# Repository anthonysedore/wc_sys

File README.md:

# wc_sys
Wireless Communication System for Electrathon

PCB designed in KiCad,

Code for ESP32 in Arduino

-read data from motor controller, battery BMS
-collect GPS data
-log all data to sdcard
-send data to pitcrew
-show important metrics and any warnings to driver
-enable recording cool videos with data synced to video time

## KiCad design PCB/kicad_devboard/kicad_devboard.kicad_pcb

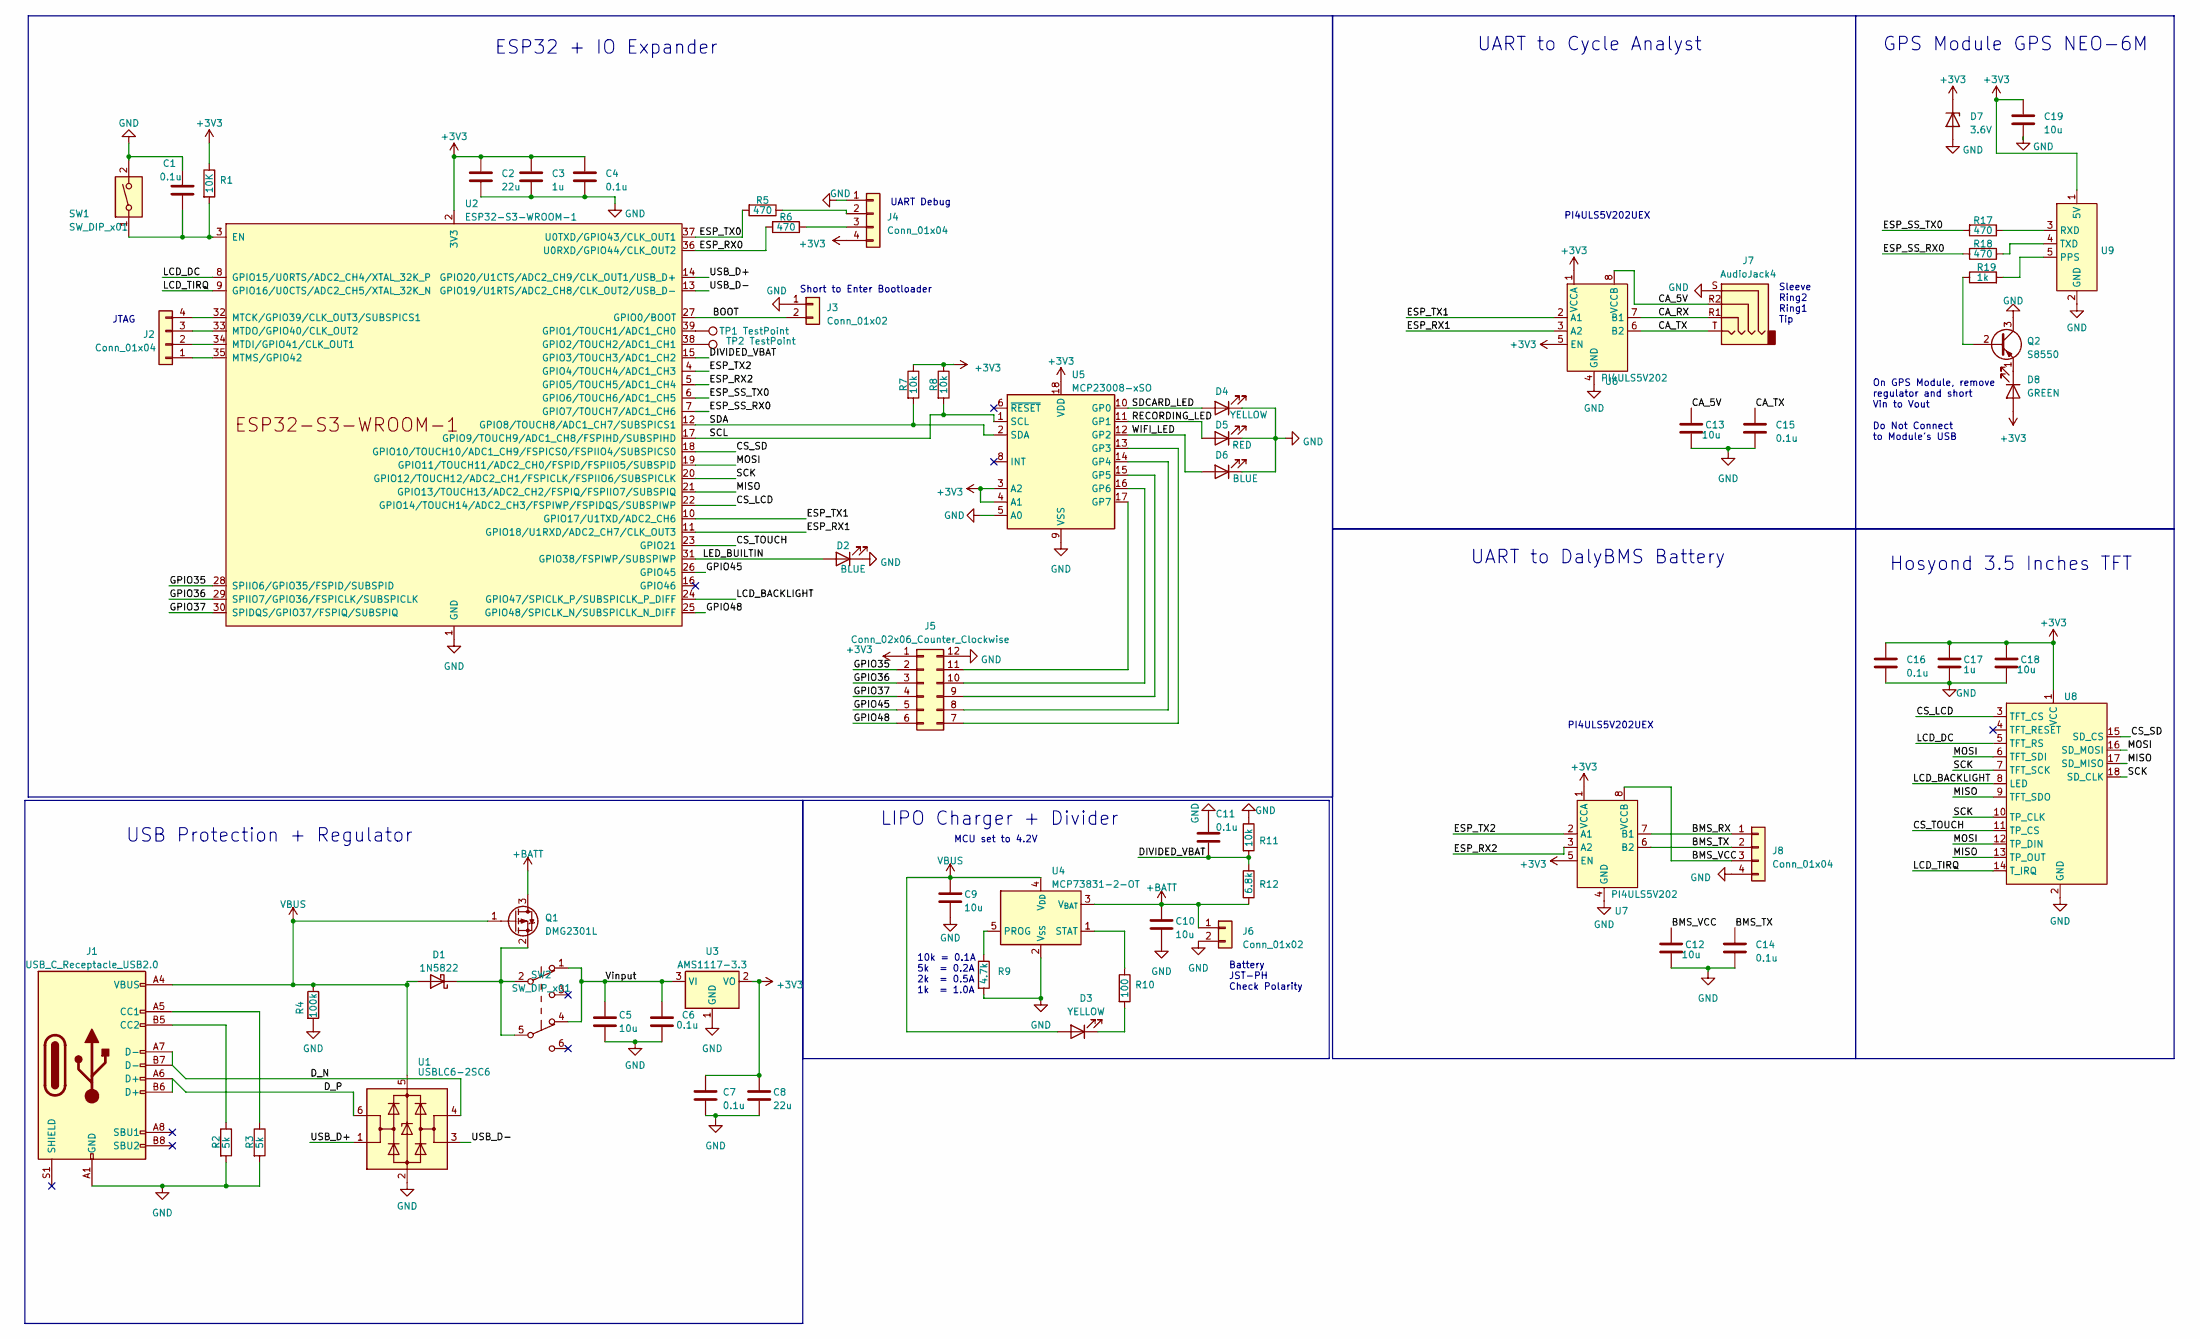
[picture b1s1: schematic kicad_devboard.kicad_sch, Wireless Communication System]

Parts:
C1, C4, C6, C7, C14, C15: 0.1u; C_0603_1608Metric
C2, C8: 22u; C_0603_1608Metric
C3: 1u; C_0603_1608Metric
C5, C19: 10u; C_0603_1608Metric
C9, C10, C12, C13: 10u; C_1206_3216Metric
C11: 0.1u; C_1206_3216Metric
C16: 0.1u; C_0805_2012Metric
C17: 1u; C_0805_2012Metric
C18: 10u; C_0805_2012Metric
D1: 1N5822; D_SMA
D2, D6: BLUE; LED_1206_3216Metric
D3, D4: YELLOW; LED_1206_3216Metric
D5: RED; LED_1206_3216Metric
D7: 3.6V; D_MiniMELF
D8: GREEN; LED_1206_3216Metric
J1: USB_C_Receptacle_USB2.0; USB_C_Receptacle_Palconn_UTC16-G
J2, J4: Conn_01x04; PinSocket_1x04_P2.54mm_Vertical
J3: Conn_01x02; PinHeader_1x02_P2.54mm_Vertical
J5: Conn_02x06_Counter_Clockwise; PinSocket_2x06_P2.54mm_Vertical
J6: Conn_01x02; JST_PH_S2B-PH-K_1x02_P2.00mm_Horizontal
J7: AudioJack4; SJ-43514-SMT_CUD
J8: Conn_01x04; JST_PH_S4B-PH-K_1x04_P2.00mm_Horizontal
Q1: DMG2301L; SOT-23
Q2: S8550; SOT-23
R1: 10K; R_1206_3216Metric
R2, R3: 5k; R_0603_1608Metric
R4: 100k; R_1206_3216Metric
R5, R6, R17, R18: 470; R_1206_3216Metric
R7, R8, R11: 10k; R_1206_3216Metric
R9: 4.7k; R_1206_3216Metric
R10: 100; R_1206_3216Metric
R12: 6.8k; R_1206_3216Metric
R19: 1k; R_1206_3216Metric
SW1: SW_DIP_x01; SW_PUSH_6mm_H5mm
SW2: SW_DIP_x01; SW_E-Switch_EG2219_DPDT_Angled
TP1, TP2: TestPoint; TestPoint_Pad_D4.0mm
U1: USBLC6-2SC6; SOT-23-6
U2: ESP32-S3-WROOM-1; ESP32-S3-WROOM-1U
U3: AMS1117-3.3; SOT-223-3_TabPin2
U4: MCP73831-2-OT; SOT-23-5
U5: MCP23008-xSO; SOIC-18W_7.5x11.6mm_P1.27mm
U6, U7: PI4ULS5V202; PI4ULS5V202UEX
U8: 3.5_inch_SPI_Module_ILI9488
U9: GT-U7

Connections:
+3V3: C2.1, C3.1, C4.1, C7.1, C8.1, C16.1, C17.1, C18.1, C19.1, D7.1 (K), D8.2 (A), J4.4, J5.1, R1.1, R7.1, R8.1, U2.2 (3V3), U3.2 (VO), U5.3 (A2), U5.4 (A1), U5.18 (VDD), U6.1 (VCCA), U6.5 (EN), U7.1 (VCCA), U7.5 (EN), U8.1 (VCC), U9.1 (5V)
+BATT: C10.1, J6.1, Q1.3 (D), R12.2, U4.3 (V_{BAT})
/BMS_RX: J8.1, U7.7 (B1)
/BMS_TX: C14.1, J8.2, U7.6 (B2)
/BMS_VCC: C12.1, J8.3, U7.8 (VCCB)
/BOOT: J3.2, U2.27 (GPIO0/BOOT)
/CA_5V: C13.1, J7.R2, U6.8 (VCCB)
/CA_RX: J7.R1, U6.7 (B1)
/CA_TX: C15.1, J7.T, U6.6 (B2)
/CS_LCD: U2.22 (GPIO14/TOUCH14/ADC2_CH3/FSPIWP/FSPIDQS/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), U8.3 (TFT_CS)
/CS_SD: U2.18 (GPIO10/TOUCH10/ADC1_CH9/FSPICS0/FSPIIO4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), U8.15 (SD_CS)
/CS_TOUCH: U2.23 (GPIO21), U8.11 (TP_CS)
/DIVIDED_VBAT: C11.2, R11.2, R12.1, U2.15 (GPIO3/TOUCH3/ADC1_CH2)
/ESP_RX0: R6.2, U2.36 (U0RXD/GPIO44/CLK_OUT2)
/ESP_RX1: U2.11 (GPIO18/U1RXD/ADC2_CH7/CLK_OUT3), U6.3 (A2)
/ESP_RX2: U2.5 (GPIO5/TOUCH5/ADC1_CH4), U7.3 (A2)
/ESP_SS_RX0: R18.2, U2.7 (GPIO7/TOUCH7/ADC1_CH6)
/ESP_SS_TX0: R17.2, U2.6 (GPIO6/TOUCH6/ADC1_CH5)
/ESP_TX0: R5.2, U2.37 (U0TXD/GPIO43/CLK_OUT1)
/ESP_TX1: U2.10 (GPIO17/U1TXD/ADC2_CH6), U6.2 (A1)
/ESP_TX2: U2.4 (GPIO4/TOUCH4/ADC1_CH3), U7.2 (A1)
/GPIO35: J5.2, U2.28 (SPIIO6/GPIO35/FSPID/SUBSPID)
/GPIO36: J5.3, U2.29 (SPIIO7/GPIO36/FSPICLK/SUBSPICLK)
/GPIO37: J5.4, U2.30 (SPIDQS/GPIO37/FSPIQ/SUBSPIQ)
/GPIO45: J5.5, U2.26 (GPIO45)
/GPIO48: J5.6, U2.25 (GPIO48/SPICLK_N/SUBSPICLK_N_DIFF)
/LCD_BACKLIGHT: U2.24 (GPIO47/SPICLK_P/SUBSPICLK_P_DIFF), U8.8 (LED)
/LCD_DC: U2.8 (GPIO15/U0RTS/ADC2_CH4/XTAL_32K_P), U8.5 (TFT_RS)
/LCD_TIRQ: U2.9 (GPIO16/U0CTS/ADC2_CH5/XTAL_32K_N), U8.14 (T_IRQ)
/LED_BUILTIN: D2.2 (A), U2.31 (GPIO38/FSPIWP/SUBSPIWP)
/MISO: U2.21 (GPIO13/TOUCH13/ADC2_CH2/FSPIQ/FSPIIO7/S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), U8.9 (TFT_SDO), U8.13 (TP_OUT), U8.17 (SD_MISO)
/MOSI: U2.19 (GPIO11/TOUCH11/ADC2_CH0/FSPID/FSPIIO5/S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), U8.6 (TFT_SDI), U8.12 (TP_DIN), U8.16 (SD_MOSI)
/RECORDING_LED: D5.2 (A), U5.11 (GP1)
/SCK: U2.20 (GPIO12/TOUCH12/ADC2_CH1/FSPICLK/FSPIIO6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), U8.7 (TFT_SCK), U8.10 (TP_CLK), U8.18 (SD_CLK)
/SCL: R8.2, U2.17 (GPIO9/TOUCH9/ADC1_CH8/FSPIHD/SUBSPIHD), U5.1 (SCL)
/SDA: R7.2, U2.12 (GPIO8/TOUCH8/ADC1_CH7/SUBSPICS1), U5.2 (SDA)
/SDCARD_LED: D4.2 (A), U5.10 (GP0)
/USB_D+: U1.1 (I/O1), U2.14 (GPIO20/U1CTS/ADC2_CH9/CLK_OUT1/USB_D+)
/USB_D-: U1.3 (I/O2), U2.13 (GPIO19/U1RTS/ADC2_CH8/CLK_OUT2/USB_D-)
/Vinput: C5.1, C6.2, SW2.1 (A), SW2.4 (A), U3.3 (VI)
/WIFI_LED: D6.2 (A), U5.12 (GP2)
GND: C1.1, C2.2, C3.2, C4.2, C5.2, C6.1, C7.2, C8.2, C9.2, C10.2, C11.1, C12.2, C13.2, C14.2, C15.2, C16.2, C17.2, C18.2, C19.2, D2.1 (K), D4.1 (K), D5.1 (K), D6.1 (K), D7.2 (A), J1.A1 (GND), J1.A12 (GND), J1.B1 (GND), J1.B12 (GND), J3.1, J4.1, J5.12, J6.2, J7.S, J8.4, Q2.3 (C), R2.2, R3.2, R4.2, R9.2, R11.1, SW1.2, U1.2 (GND), U2.1 (GND), U2.40 (GND), U2.41 (GND), U3.1 (GND), U4.2 (V_{SS}), U5.5 (A0), U5.9 (VSS), U6.4 (GND), U7.4 (GND), U8.2 (GND), U9.2 (GND)
unnamed: D1.1 (K), Q1.2 (S), SW2.2 (B), SW2.5 (B)
unnamed: D3.1 (K), R10.2
unnamed: D8.1 (K), Q2.1 (E)
unnamed: J1.A5 (CC1), R3.1
unnamed: J1.B5 (CC2), R2.1
unnamed: J2.1, U2.35 (MTMS/GPIO42)
unnamed: J2.2, U2.34 (MTDI/GPIO41/CLK_OUT1)
unnamed: J2.3, U2.33 (MTDO/GPIO40/CLK_OUT2)
unnamed: J2.4, U2.32 (MTCK/GPIO39/CLK_OUT3/SUBSPICS1)
unnamed: J4.2, R5.1
unnamed: J4.3, R6.1
unnamed: J5.7, U5.13 (GP3)
unnamed: J5.8, U5.14 (GP4)
unnamed: J5.9, U5.15 (GP5)
unnamed: J5.10, U5.16 (GP6)
unnamed: J5.11, U5.17 (GP7)
unnamed: Q2.2 (B), R19.1
unnamed: C1.2, R1.2, SW1.1, U2.3 (EN)
unnamed: TP1.1, U2.39 (GPIO1/TOUCH1/ADC1_CH0)
unnamed: TP2.1, U2.38 (GPIO2/TOUCH2/ADC1_CH1)
unnamed: R9.1, U4.5 (PROG)
unnamed: R10.1, U4.1 (STAT)
unnamed: R19.2, U9.5 (PPS)
unnamed: R17.1, U9.3 (RXD)
unnamed: R18.1, U9.4 (TXD)
VBUS: C9.1, D1.2 (A), D3.2 (A), J1.A4 (VBUS), J1.A9 (VBUS), J1.B4 (VBUS), J1.B9 (VBUS), Q1.1 (G), R4.1, U1.5 (VBUS), U4.4 (V_{DD})

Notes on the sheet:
UART to DalyBMS Battery
Hosyond 3.5 Inches TFT
10k = 0.1A 5k = 0.2A 2k = 0.5A 1k = 1.0A
PI4ULS5V202UEX
USB Protection + Regulator
UART Debug
On GPS Module, remove regulator and short Vin to Vout Do Not Connect to Module's USB
GPS Module GPS NEO-6M
LIPO Charger + Divider
ESP32 + IO Expander
UART to Cycle Analyst
JTAG
Sleeve Ring2 Ring1 Tip
MCU set to 4.2V
Battery JST-PH Check Polarity
Short to Enter Bootloader

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
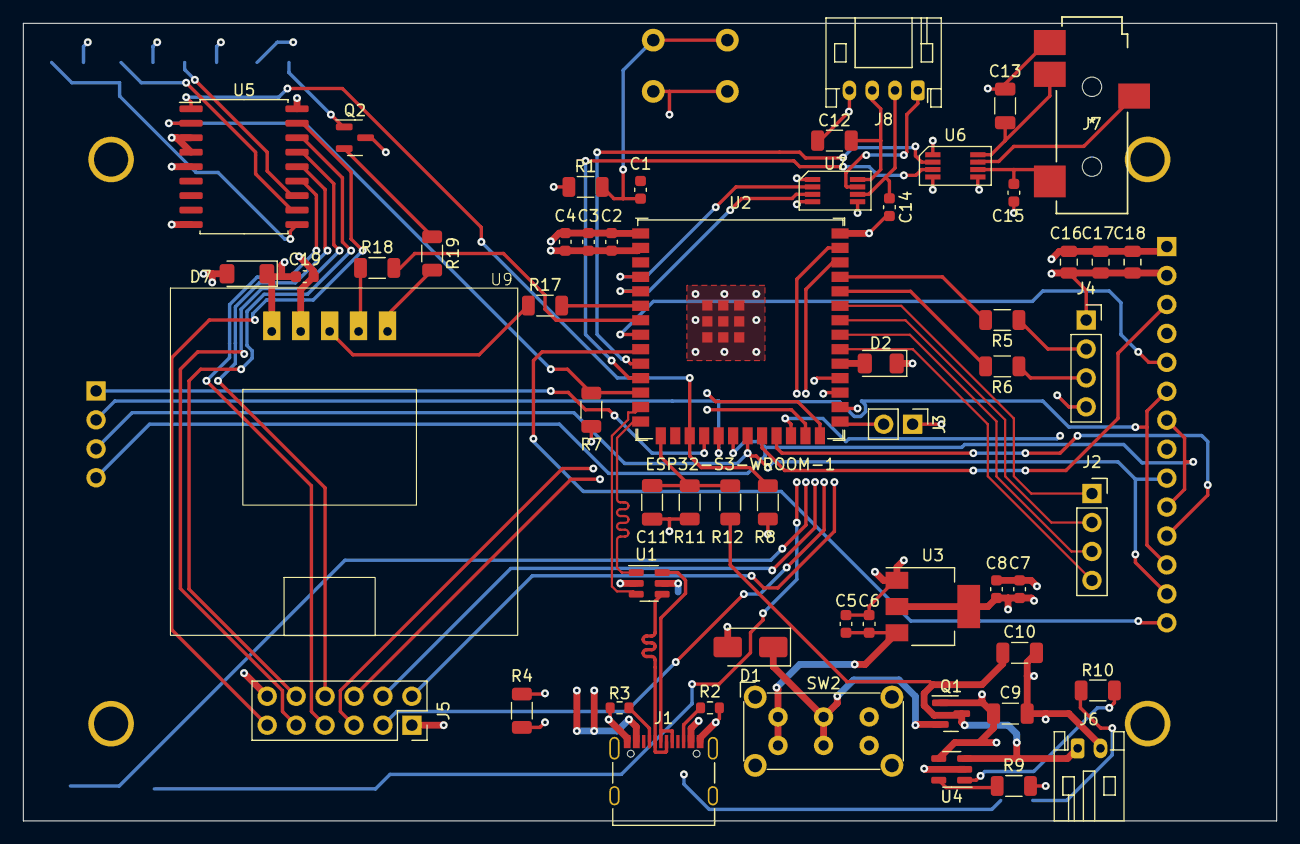
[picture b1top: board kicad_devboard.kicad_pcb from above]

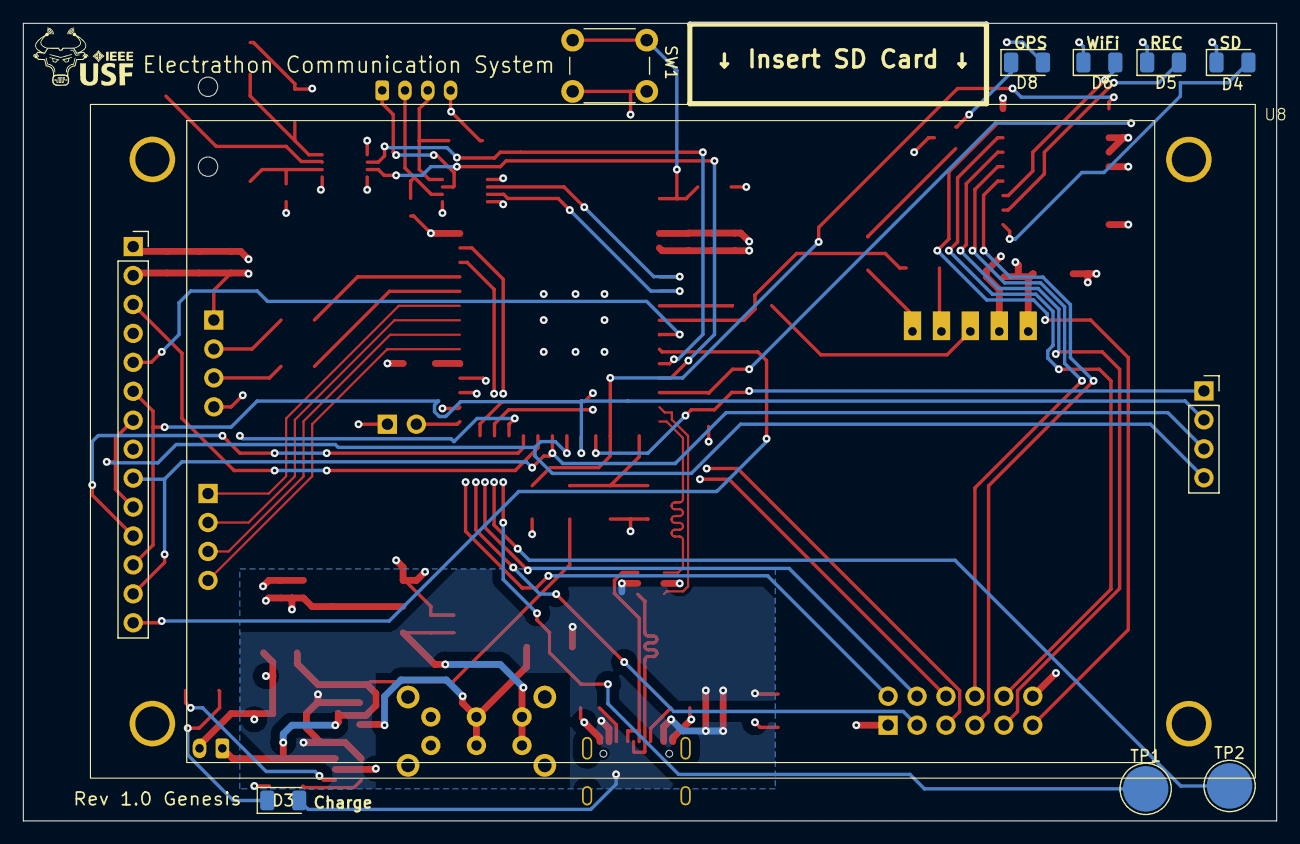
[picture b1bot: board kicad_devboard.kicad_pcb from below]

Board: 4 copper layers, 110.0 x 70.0 mm, 65 parts (9 on the bottom side), 70 nets.

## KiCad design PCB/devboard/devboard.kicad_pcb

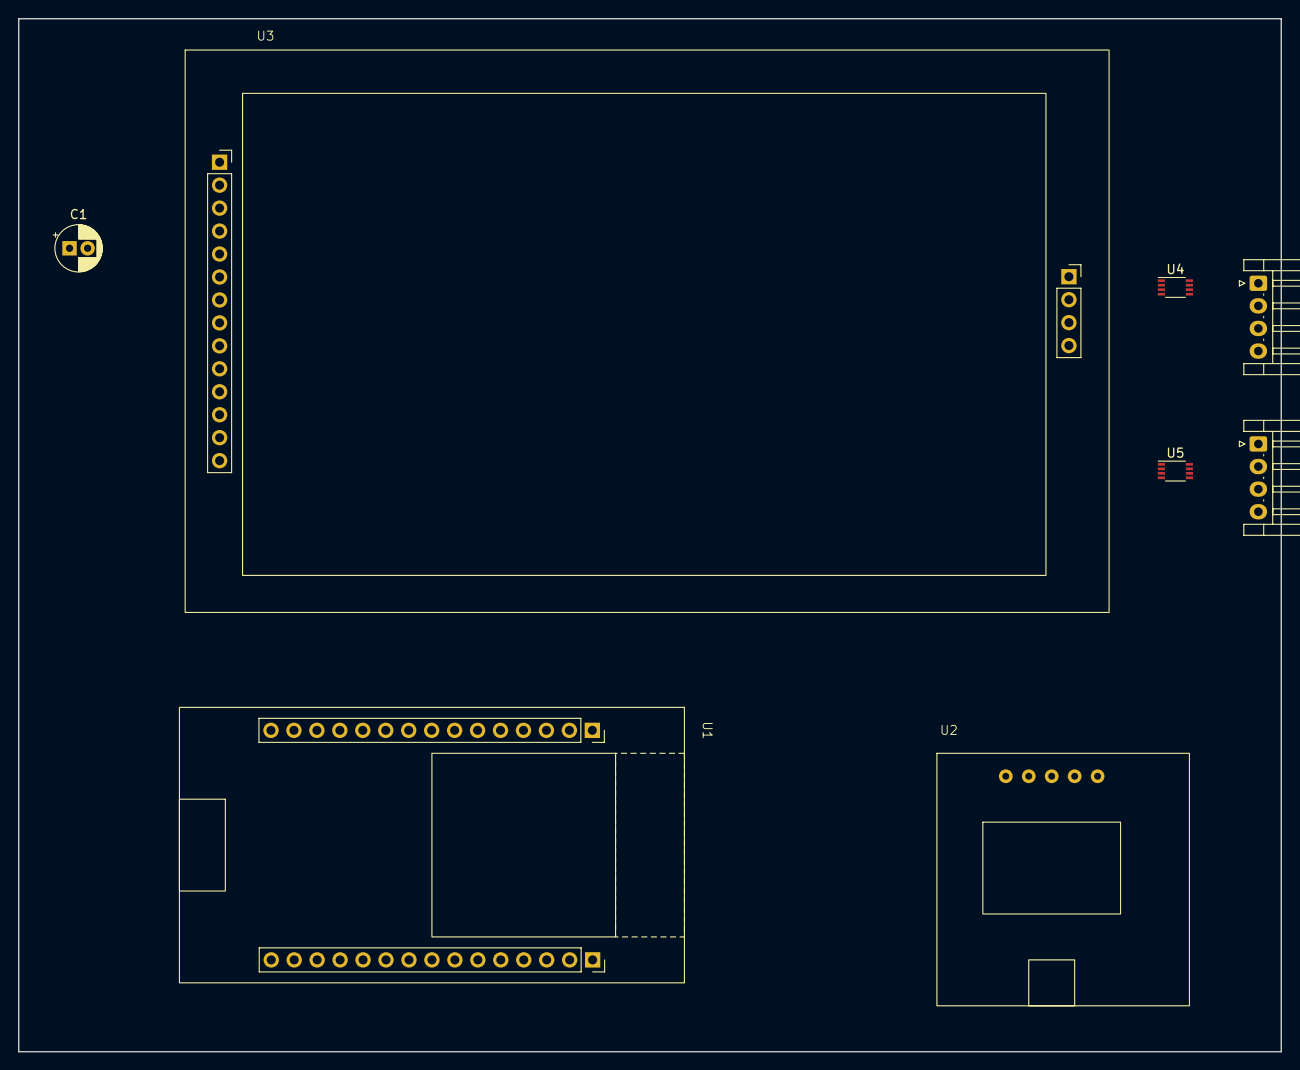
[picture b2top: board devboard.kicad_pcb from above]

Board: 2 copper layers, 139.7 x 114.3 mm, 8 parts (0 on the bottom side), 22 nets, no tracks yet.

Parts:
C1: 10uF; CP_Radial_D5.0mm_P2.00mm
J1, J2: Conn_01x04; JST_EH_S4B-EH_1x04_P2.50mm_Horizontal
U1: esp32dev
U2: NEO-6M
U3: LCD3.5tft
U4, U5: 74LVC2T45DC; VSSOP-8_2.3x2mm_P0.5mm

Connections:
+3.3V: C1.1, U1.41 (VCC), U3.1 (VCC), U3.8 (LED), U4.1 (VCCA), U5.1 (VCCA)
+5V: U1.40 (VIN), U2.1 (5V)
/MISO: U1.19 (D19), U3.13 (T_DO)
/MOSI: U1.23 (IO23), U3.6 (MOSI), U3.12 (T_DIN)
/RX2: U1.16 (RX2), U2.4 (TX0)
/SCLK: U1.18 (D18), U3.7 (SCK), U3.10 (T_CLK)
/SS_RX1: U1.34 (D34), U4.2 (1A)
/SS_RX2: U1.35 (D35), U5.2 (1A)
/SS_TX1: U1.13 (D13), U4.3 (2A)
/SS_TX2: U1.14 (D14), U5.3 (2A)
/TFT_CS: U1.15 (D15), U3.3 (CS)
/TFT_DC: U1.2 (D2), U3.5 (DC/RS)
/TFT_RST: U1.4 (D4), U3.4 (RESET)
/TOUCH_CS: U1.21 (D21), U3.11 (T_CS)
/TX2: U1.17 (TX2), U2.3 (RXD)
GND: C1.2, J1.4, U1.42 (GND), U2.2 (GND), U3.2 (GND), U4.4 (GND), U5.4 (GND)
unnamed: J1.1, U4.8 (VCCB)
unnamed: J1.2, U4.7 (1B)
unnamed: J1.3, U4.6 (2B)
unnamed: J2.1, U5.8 (VCCB)
unnamed: J2.2, U5.7 (1B)
unnamed: J2.3, U5.6 (2B)

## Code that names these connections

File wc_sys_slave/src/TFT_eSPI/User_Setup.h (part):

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// The DC (Data Command) pin may be labelled AO or RS (Register Select)
//
// With some displays such as the ILI9341 the TFT CS pin can be connected to GND if no more
// SPI devices (e.g. an SD Card) are connected, in this case comment out the #define TFT_CS
// line below so it is NOT defined. Other displays such at the ST7735 require the TFT CS pin
// to be toggled during setup, so in these cases the TFT_CS line must be defined and connected.
//
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// ###### EDIT THE PIN NUMBERS IN THE LINES FOLLOWING TO SUIT YOUR ESP8266 SETUP ######

// For NodeMCU - use pin numbers in the form PIN_Dx where Dx is the NodeMCU pin designation
// #define TFT_CS   PIN_D8  // Chip select control pin D8
// #define TFT_DC   PIN_D3  // Data Command control pin
// #define TFT_RST  PIN_D4  // Reset pin (could connect to NodeMCU RST, see next line)
//#define TFT_RST  -1    // Set TFT_RST to -1 if the display RESET is connected to NodeMCU RST or 3.3V

//#define TFT_BL PIN_D1  // LED back-light (only for ST7789 with backlight control pin)

//#define TOUCH_CS PIN_D2     // Chip select pin (T_CS) of touch screen

//#define TFT_WR PIN_D2       // Write strobe for modified Raspberry Pi TFT only

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//#define TFT_SPI_OVERLAP

// In ESP8266 overlap mode the TFT chip select MUST connect to pin D3
//#define TFT_CS   PIN_D3
//#define TFT_DC   PIN_D5  // Data Command control pin
//#define TFT_RST  PIN_D4  // Reset pin (could connect to NodeMCU RST, see next line)
//#define TFT_RST  -1  // Set TFT_RST to -1 if the display RESET is connected to NodeMCU RST or 3.3V


// ###### EDIT THE PIN NUMBERS IN THE LINES FOLLOWING TO SUIT YOUR ESP32 SETUP   ######
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#define TFT_MISO 19
#define TFT_MOSI 23
#define TFT_SCLK 18
#define TFT_CS   15  // Chip select control pin
#define TFT_DC    2  // Data Command control pin
#define TFT_RST   4  // Reset pin (could connect to RST pin)
//#define TFT_RST  -1  // Set TFT_RST to -1 if display RESET is connected to ESP32 board RST

// For ESP32 Dev board (only tested with GC9A01 display)
// The hardware SPI can be mapped to any pins

//#define TFT_MOSI 15 // In some display driver board, it might be written as "SDA" and so on.
//#define TFT_SCLK 14
//#define TFT_CS   5  // Chip select control pin
//#define TFT_DC   27  // Data Command control pin
//#define TFT_RST  33  // Reset pin (could connect to Arduino RESET pin)
//#define TFT_BL   22  // LED back-light

#define TOUCH_CS 21     // Chip select pin (T_CS) of touch screen

//#define TFT_WR 22    // Write strobe for modified Raspberry Pi TFT only

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//#define TFT_MISO 19
//#define TFT_MOSI 23
//#define TFT_SCLK 18
//#define TFT_CS   14  // Chip select control pin
//#define TFT_DC   27  // Data Command control pin
//#define TFT_RST  33  // Reset pin (could connect to Arduino RESET pin)
//#define TFT_BL   32  // LED back-light (required for M5Stack)

// ######       EDIT THE PINs BELOW TO SUIT YOUR ESP32 PARALLEL TFT SETUP        ######
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//#define TFT_PARALLEL_8_BIT

// The ESP32 and TFT the pins used for testing are:
//#define TFT_CS   33  // Chip select control pin (library pulls permanently low
//#define TFT_DC   15  // Data Command control pin - must use a pin in the range 0-31
//#define TFT_RST  32  // Reset pin, toggles on startup

//#define TFT_WR    4  // Write strobe control pin - must use a pin in the range 0-31
//#define TFT_RD    2  // Read strobe control pin
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//#define TFT_SCLK PB13

// Can use Ardiuno pin references, arbitrary allocation, TFT_eSPI controls chip select
//#define TFT_CS   D5 // Chip select control pin to TFT CS
//#define TFT_DC   D6 // Data Command control pin to TFT DC (may be labelled RS = Register Select)
//#define TFT_RST  D7 // Reset pin to TFT RST (or RESET)
// OR alternatively, we can use STM32 port reference names PXnn
//#define TFT_CS   PE11 // Nucleo-F767ZI equivalent of D5
//#define TFT_DC   PE9  // Nucleo-F767ZI equivalent of D6
//#define TFT_RST  PF13 // Nucleo-F767ZI equivalent of D7

//#define TFT_RST  -1   // Set TFT_RST to -1 if the display RESET is connected to processor reset
                        // Use an Arduino pin for initial testing as connecting to processor reset
                        // may not work (pulse too short at power up?)

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
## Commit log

2023-06-09 Added Schematic Files and Arduino Code
2023-06-09 Selected wrong out of date directory in previous commit
2023-06-09 created finalboard kicad file with esp32 chip, configured footprints&symbol for esp32s3 1u
2023-06-10 Added ESP NOW arduino tests
2023-06-10 Added GPS unit tests using software serial
    ESP32 has 3 UART's, 1 of them is for flashing and debugging. Electrathon car has bms which communicates through UART and cycle analyst also UART. Software Serial allows esp32 to communicate to UART d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
2023-07-01 freertos arduino
    freertos examples with screen & gps
2023-07-02 Included Libraries
    -Included copy of libraries used alongside configuration
    -For different setups .h files may need to change for eSPI TFT display
2023-07-02 LCD Screen update
2023-07-02 FinalBoard Changes
2023-07-02 Added Data Task
    To log data, keep track of time
2023-07-02 Definitions.h
    To move global variables outside of task.h's
2023-07-03 Changed data loop start and end
    int toggleDATA -> bool dataActive
    may change to another bool variable name to make clearer
2023-07-08 Added ESP32Time Library
    To load time into RTC
    Also added RTC test example using -5 GMT offset time
2023-07-09 SD logging support
    logs every 0.1, task takes 10Kb ram
2023-07-11 Test using prototype data
    https://youtu.be/UrNn4R37eiI
2023-07-11 Design Iterations
    added touch buttons
    wired SPI sdcard and display
2023-07-11 ESP Now tests
    working on esp now tests
2023-07-11 Edit
2023-07-14 GOPro Initial Tests
2023-07-16 Improved Data Accuracy and GPS sample
    -Changed SD to append every 200 ms instead of every 100 ms
    -Changed GPS sample rate to every 1 sec instead of 10 seconds
    -Instead of relying on delays to keep track of time, use hardware timer to keep track of exact time and not lose sync
2023-07-16 Time Tests
    using hardware timer of esp32
2023-07-16 Reorganized Tests
    SDcard folder, communication folder, and website folder for many tests pertaining to each group
2023-08-07 Added Components
    added lipo charger, regulator, removed type B usb, added 3d Models
2023-08-10 Incorporated Feedback
2023-08-10 Schematic Mostly Done
    check esp32 pins
2023-08-12 Fixed Footprints, connected all nets
2023-08-18 routing initial
2023-08-20 Added Fake Speed Function
    used to demo the screen without any real data from car
2023-08-20 Update TFT_eSPI.zip
    Updated header config, if config is not correct wrong pins will be used, wrong colors displayed, wrong display driver
2023-08-20 iterations
2023-09-02 pcb made genesis 1.0
    pcb made and manufactured
2023-09-12 Reorganized for public, genesis1.0board info
2023-09-13 Added settings for genesis board
    to get serial data communicating and utilize storage space
2023-09-13 add modules used
2024-01-26 code
    switched begin activation to boot button
    added cycle analyst task.cpp
    removements in lcd task
2024-02-02 Removed Softwareserial
    software serial for gps is now Serial1
2024-02-03 Cycle Analyst Demo
2024-02-03 Disabled Date Record
    was causing crashing when gps couldnt receive time, setTime = true to undo
2024-02-03 Cycle Analyst Task and Display on LCD
    numerous bug fixes to cycle analyst task
    dont forget to use forever loop in tasks created or will crash
2024-02-03 Changed memory given to CA task
2024-02-03 Added CA logs to Data Task
    still buggy and needs more testing and debugging
2024-02-05 Fixed Bug of Stop Recording and CSV log file
    dataentry variable needed to be bigger
    data entry task moved to other core, hardware timer would keep messing up when cycle analyst was read
2024-02-10 GPS bugged
